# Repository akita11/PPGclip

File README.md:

# PPG Clip

[M5Stack社の心拍センサユニット](https://www.switch-science.com/products/5695)を利用した、測定精度・安定度の高い透過型の光学脈波(PPG)計測器です。
マイコン部はM5Stack社のATOMシリーズを取り付けらて一体化できます。
部品セットからこれらを組み立てることができます。

ATOMシリーズを使わずに、直接Groveケーブルを接続して、他のM5Stackシリーズ等のマイコンで使用することもできます。

## 必要なもの
- 部品セット（筐体（4点）、LED基板、コネクタ基板、4p/2mmピンソケット×2、ケーブル（色が写真のものと異なる場合があります）、M2.3×8mmタッピングねじ、M2×4mmねじ、押しバネ0.7×7.5×23）
- [M5Stack社の心拍センサユニット](https://www.switch-science.com/products/5695)
- M5Stack社ATOMシリーズ（ディスプレイのついている[ATOMS3](https://www.switch-science.com/products/8670)が脈波確認などができて便利。ATOMS3用のサンプルファームウエアあり）
- 工具（1.5mm六角レンチ、小プラスドライバ）

# 組み立て

1. 心拍センサユニットを、1.5mm六角レンチを使って分解し、中のボード(1)を取り出します。
1. LED基板(2)とボード(1)を、ケーブル(3)でFig1のようにはんだ付けして接続します。ケーブルの対応関係を間違えないように注意してください。このとき、ボード(1)側は、ケーブルを横側に引き出し、はんだづけ箇所がなるべく平坦になるようにします。
1. コネクタ基板(4)に、4p/2mmピンソケット(5)を2個、傾かないように注意してはんだ付けし、足をなるべく短くカットします。（Fig2）
1. ボード(1)にコネクタ基板(4)を差し込み、Fig3のように筐体(6）にはめます。ケーブル(3)は、図のように上面基板に重ならないようにします。
1. ATOMシリーズを、コネクタ基板(4)の反対側にさしこみ、M2ねじ(7)でFig3のように固定します。
1. 黒い筐体(8)を筐体(6)（向きに注意）に、4個のタッピングねじ(9)でFig4のように固定します。
1. 筐体(9)に、LED基板(2)をFig5のようにはめ、黒い筐体(10)（向きに注意）を、4個のタッピングねじ(9)でFig6のように固定します。
1. Fig7のように、ばね(10)を筐体(9)にはめ、その後、Fig8のように、ばね(10)を反対側の筐体(6)にはめつつ、2つの筐体を押し込んではめこみます。
1. ATOMシリーズにプログラムを書き込み、ボード(1)が動作すると、Fig9のように上下両側のLEDが点灯します。

Fig1.:

Fig2:

Fig3:

Fig4:

Fig5:

Fig6:

Fig7:

Fig8:

Fig9:

# ソフトウエア

M5Stack社の心拍センサユニット用のプログラムはすべて利用できます。サンプルとして、以下の機能をもつATOMS3用のプログラムがsampleFW/内にあります。
- 波形表示(100Hzサンプリング)
- ベースライン変動除去
- 簡易な正常計測チェック（正常計測時は緑色のグラフ）
- ボタンを押すと10秒分の生データをUSU UARTにCSV形式で出力

## Author

Junichi Akita (@akita11) / akita@ifdl.jp

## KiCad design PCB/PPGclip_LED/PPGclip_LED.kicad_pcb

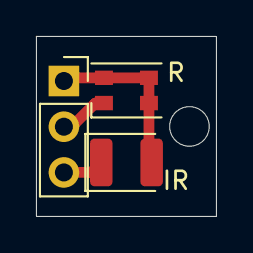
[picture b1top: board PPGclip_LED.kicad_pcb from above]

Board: 2 copper layers, 10.0 x 10.0 mm, 3 parts (0 on the bottom side), 3 nets.

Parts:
D1: LED; LED_1210_3225Metric
D2: LED; LED_Cree-PLCC4_3.2x2.8mm_CCW
J1: Conn_01x03; PinSocket_1x03_P2.54mm_Vertical

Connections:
unnamed: D1.1 (K), J1.3
unnamed: D1.2 (A), D2.2 (A), J1.1
unnamed: D2.1 (K), J1.2

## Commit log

2025-12-01 resume after transfer by FIFO reset
2025-12-02 add filtering&valid check (not tested)
2025-12-03 filter&validation works (slope not checked)
2026-01-09 add README
2026-01-09 add STL&PCB
2026-01-11 STL fix
2026-01-28 add photo with Grove cable
2026-01-29 typo fix in README
